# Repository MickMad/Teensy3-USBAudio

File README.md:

Teensy3-USBAudio
================

Transform a Teensy 3.0 in a USB compliant audio device

Software part
-------------------------

The `software` folder contains modified versions of some Teensy 3.0 USB core library.

First, in `/hardware/teensy` there's the board.txt file which has some added lines to properly show the "Audio" USB type in the Arduino IDE;

In `/hardware/teensy/teensy3` there are some USB core library files for the Teensy 3.0 with my Audio library patch.

The `usb_audio.c` and `usb_audio.h` files are the real Audio library, which is going to handle all the audio interface relevant stuff.

The `usb_desc.c` and `usb_desc.h` files contain USB descriptors-related stuff; some configuration stuff is in `usb_desc.h`, while the whole Audio interface descriptor is in `usb_audio.c`.

The `usb_dev.c` and `usb_dev.h` files contain low level USB control stuff; the only "major" modification until now is that there's no toggle between Data0 and Data1 PIDs when sending packets on the Audio Streaming interface, because Isochronous transfers only happen to use Data0 PIDs.

The `usb_inst.cpp` file contains all the USB application-specific library instances to be used in the sketches.

In `sketch` you'll find a sketch folder, which contains the sketch `BlinkAndTalk.ino`; this sketch instantiates an IntervalTimer, then waits until the host requests the Audio Interface to stream data; then it starts the timer to generate samples and streams them via USB.

I know the name BlinkAndTalk doesn't really fit the Audio functionality, but that started as a pure USB initialization debugging sketch that blinked and "talked" via SPI to an Arduino that was used as a Serial-to-USB converter, to let me know what was actually happening during the USB initialization and interrupt routines :D

Right now, the descriptor configures the Teensy as a device called Teensy Audio (but it may show as Teensyduino MIDI on Linux, don't know why), and it will show up as a Mono Microphone input, 8KHz , 16 bits per sample.
The sketch SHOULD be sending a 1 KHz square wave, although recording it in Audacity @ 8 KHz shows a 1KHz carrier with a 4 KHz triangle over it, even if a USB packet analyzer shows the same data you see in the sketch (0x8000 - 0x7fff).
I still got to understand why this happens; I've tried filling the packets LSB first, MSB first, don't-care-just-write-stuff first, I just can't get it to show as a square wave. Though, if you record in Audacity @ 44100 or whatever it's not 8KHz, it shows a nice square wave. Gotta investigate further.

All the stuff inside the software folder must be placed in the same directory found in your arudino folder.

***WARNING: MAKE A BACKUP COPY OF THOSE FILES IN YOUR ARDUINO FOLDER BEFORE MAKING ANY CHANGES.***

I know my mods are harmless, and that they are never ever used unless you explicitly set the Audio USB Type when compiling, but you should backup anyway, I don't want to be blamed for anything :V

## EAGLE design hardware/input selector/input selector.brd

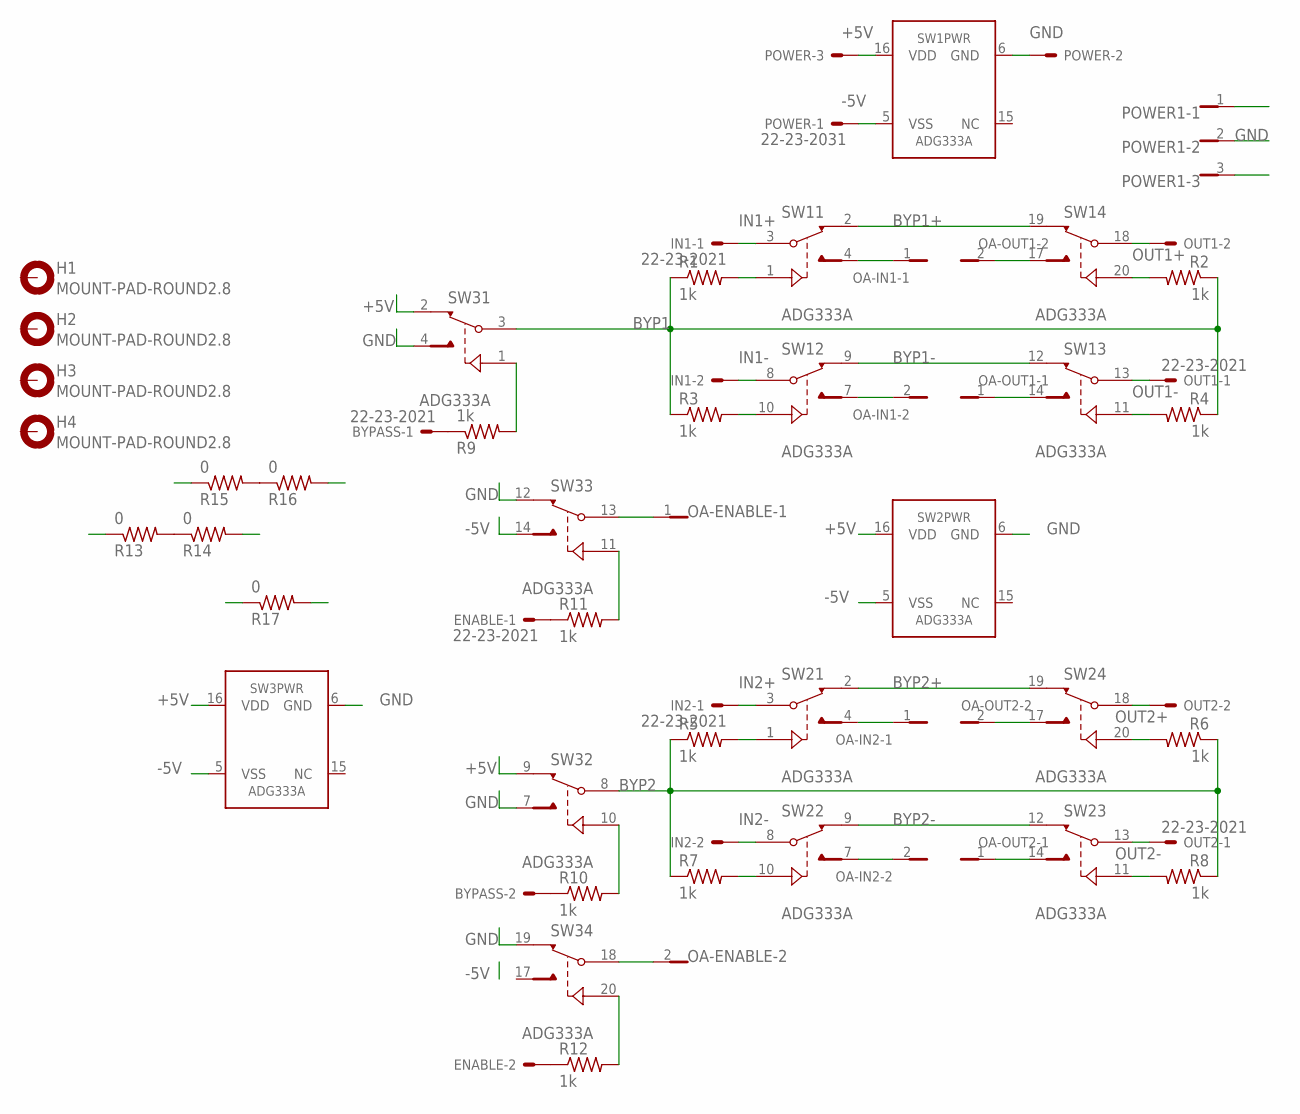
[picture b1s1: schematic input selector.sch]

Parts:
BYPASS: 22-23-2021
ENABLE: 22-23-2021
H1, H2, H3, H4: MOUNT-PAD-ROUND2.8; 2,8-PAD
IN1, IN2: 22-23-2021
OA-ENABLE: FE02-1
OA-IN1, OA-IN2: FE02-1
OA-OUT1, OA-OUT2: FE02-1
OUT1, OUT2: 22-23-2021
POWER: 22-23-2031
POWER1: FE03-1
R1, R2, R3, R4, R5, R6, R7, R8, R9, R10, R11, R12: 1k; R0603
R13, R14, R15, R16, R17: 0; R0603
SW1, SW2, SW3: ADG333A; SSOP20

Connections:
+5V: POWER.3, POWER1.1, R17.1, R17.2, SW1.16 (VDD), SW2.16 (VDD), SW3.2 (A), SW3.9 (A), SW3.16 (VDD)
-5V: POWER.1, POWER1.3, SW1.5 (VSS), SW2.5 (VSS), SW3.5 (VSS), SW3.14 (B)
BYP1: R1.1, R2.1, R3.1, R4.1, R13.1, R14.2, SW3.3 (D)
BYP1+: SW1.2 (A), SW1.19 (A)
BYP1-: SW1.9 (A), SW1.12 (A)
BYP2: R5.1, R6.1, R7.1, R8.1, R15.1, R16.2, SW3.8 (D)
BYP2+: SW2.2 (A), SW2.19 (A)
BYP2-: SW2.9 (A), SW2.12 (A)
GND: POWER.2, POWER1.2, SW1.6 (GND), SW2.6 (GND), SW3.4 (B), SW3.6 (GND), SW3.7 (B), SW3.12 (A), SW3.19 (A)
IN1+: IN1.1, SW1.3 (D)
IN1-: IN1.2, SW1.8 (D)
IN2+: IN2.1, SW2.3 (D)
IN2-: IN2.2, SW2.8 (D)
unnamed: ENABLE.2, R12.1
unnamed: R1.2, SW1.1 (IN)
unnamed: R5.2, SW2.1 (IN)
unnamed: R3.2, SW1.10 (IN)
unnamed: ENABLE.1, R11.1
unnamed: R7.2, SW2.10 (IN)
unnamed: OA-ENABLE.2, SW3.18 (D)
unnamed: OA-ENABLE.1, SW3.13 (D)
unnamed: R9.2, SW3.1 (IN)
unnamed: R10.2, SW3.10 (IN)
unnamed: R11.2, SW3.11 (IN)
unnamed: R12.2, SW3.20 (IN)
unnamed: OA-IN1.1, SW1.4 (B)
unnamed: R15.2, R16.1
unnamed: R13.2, R14.1
unnamed: R6.2, SW2.20 (IN)
unnamed: R2.2, SW1.20 (IN)
unnamed: R8.2, SW2.11 (IN)
unnamed: R4.2, SW1.11 (IN)
unnamed: BYPASS.1, R9.1
unnamed: BYPASS.2, R10.1
OA-IN1-: OA-IN1.2, SW1.7 (B)
OA-IN2+: OA-IN2.1, SW2.4 (B)
OA-IN2-: OA-IN2.2, SW2.7 (B)
OA-OUT1: OA-OUT1.1, SW1.14 (B)
OA-OUT1+: OA-OUT1.2, SW1.17 (B)
OA-OUT2+: OA-OUT2.2, SW2.17 (B)
OA-OUT2-: OA-OUT2.1, SW2.14 (B)
OUT1+: OUT1.2, SW1.18 (D)
OUT1-: OUT1.1, SW1.13 (D)
OUT2+: OUT2.2, SW2.18 (D)
OUT2-: OUT2.1, SW2.13 (D)

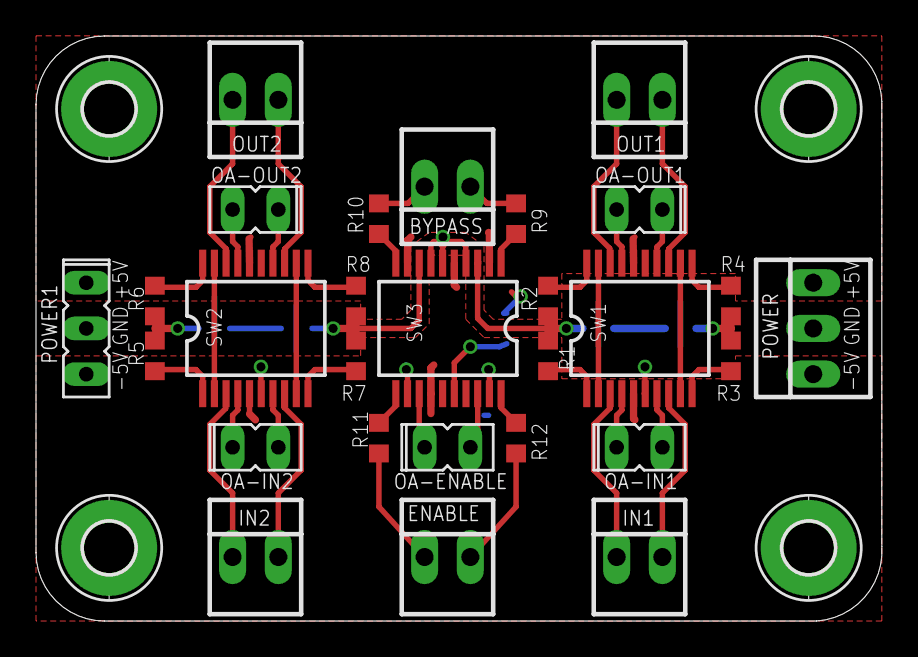
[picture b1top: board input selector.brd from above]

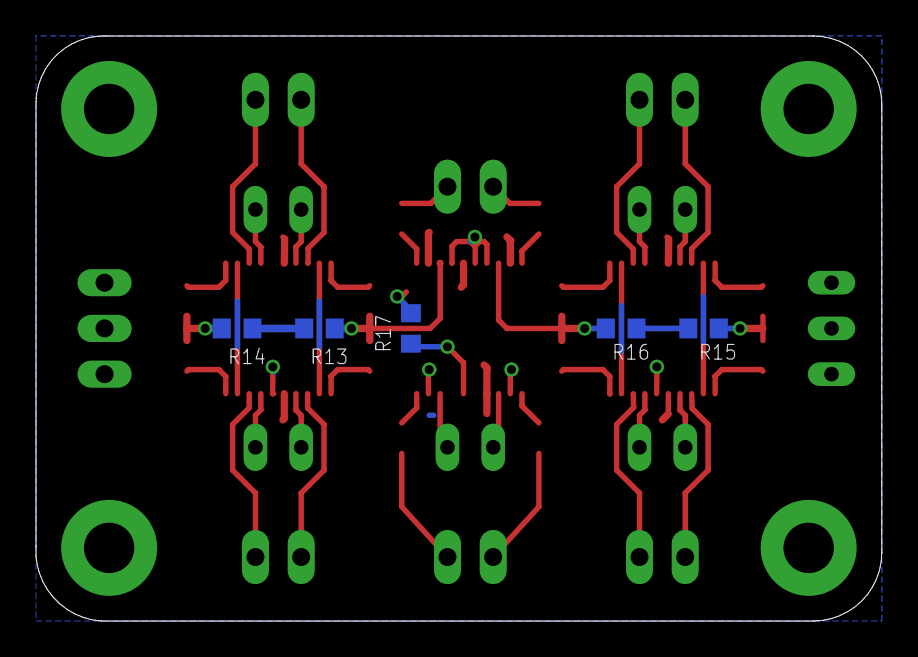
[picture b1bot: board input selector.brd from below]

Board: 2 copper layers, 47.0 x 32.5 mm, 37 parts (5 on the bottom side), 45 nets.

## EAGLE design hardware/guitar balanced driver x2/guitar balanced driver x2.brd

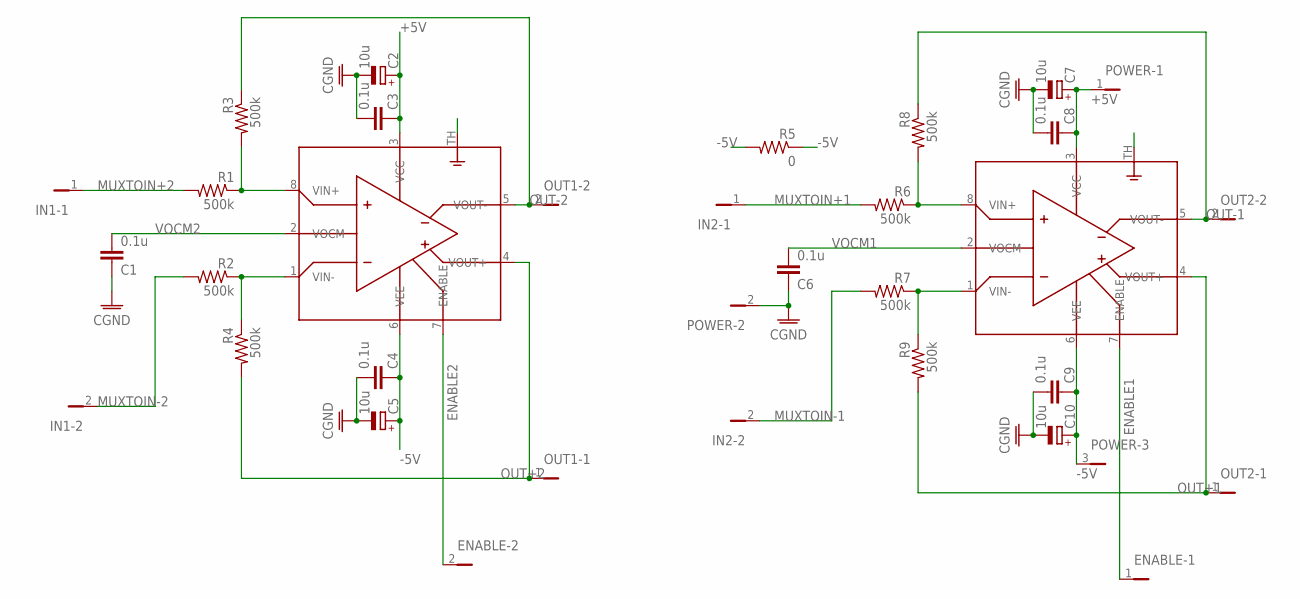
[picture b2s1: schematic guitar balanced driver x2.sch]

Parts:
C1, C3, C4, C6, C8, C9: 0.1u; C0603
C2, C5, C7, C10: 10u; PANASONIC_A
ENABLE: PINHD-1X2; 1X02
IN1, IN2: PINHD-1X2; 1X02
OA1, OA2: LME49724; S-PDSO-G08
OUT1, OUT2: PINHD-1X2; 1X02
POWER: PINHD-1X3; 1X03
R1, R2, R3, R4, R6, R7, R8, R9: 500k; R0603
R5: 0; R0603

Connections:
+5V: C2.+, C3.1, C7.+, C8.1, OA1.3 (VCC), OA2.3 (VCC), POWER.1
-5V: C4.1, C5.+, C9.1, C10.+, OA1.6 (VEE), OA1.TH (POWERPAD), OA2.6 (VEE), OA2.TH (POWERPAD), POWER.3, R5.1, R5.2
CGND: C1.1, C2.-, C3.2, C4.2, C5.-, C6.1, C7.-, C8.2, C9.2, C10.-, POWER.2
ENABLE1: ENABLE.1, OA2.7 (ENABLE)
ENABLE2: ENABLE.2, OA1.7 (ENABLE)
MUXTOIN+1: IN2.1, R6.2
MUXTOIN+2: IN1.1, R1.2
MUXTOIN-1: IN2.2, R7.2
MUXTOIN-2: IN1.2, R2.2
OUT+1: OA2.4 (VOUT+), OUT2.1, R9.2
OUT+2: OA1.4 (VOUT+), OUT1.1, R4.2
OUT-1: OA2.5 (VOUT-), OUT2.2, R8.1
OUT-2: OA1.5 (VOUT-), OUT1.2, R3.1
VIN+1: OA2.8 (VIN+), R6.1, R8.2
VIN+2: OA1.8 (VIN+), R1.1, R3.2
VIN-1: OA2.1 (VIN-), R7.1, R9.1
VIN-2: OA1.1 (VIN-), R2.1, R4.1
VOCM1: C6.2, OA2.2 (VOCM)
VOCM2: C1.2, OA1.2 (VOCM)

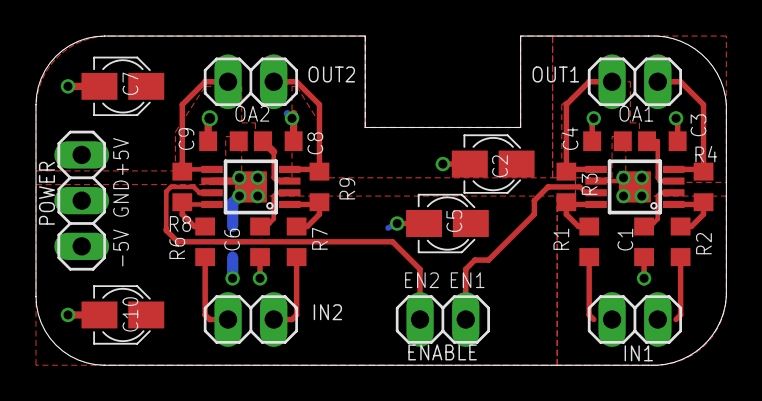
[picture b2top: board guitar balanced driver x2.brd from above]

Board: 2 copper layers, 38.4 x 18.3 mm, 27 parts (1 on the bottom side), 19 nets.

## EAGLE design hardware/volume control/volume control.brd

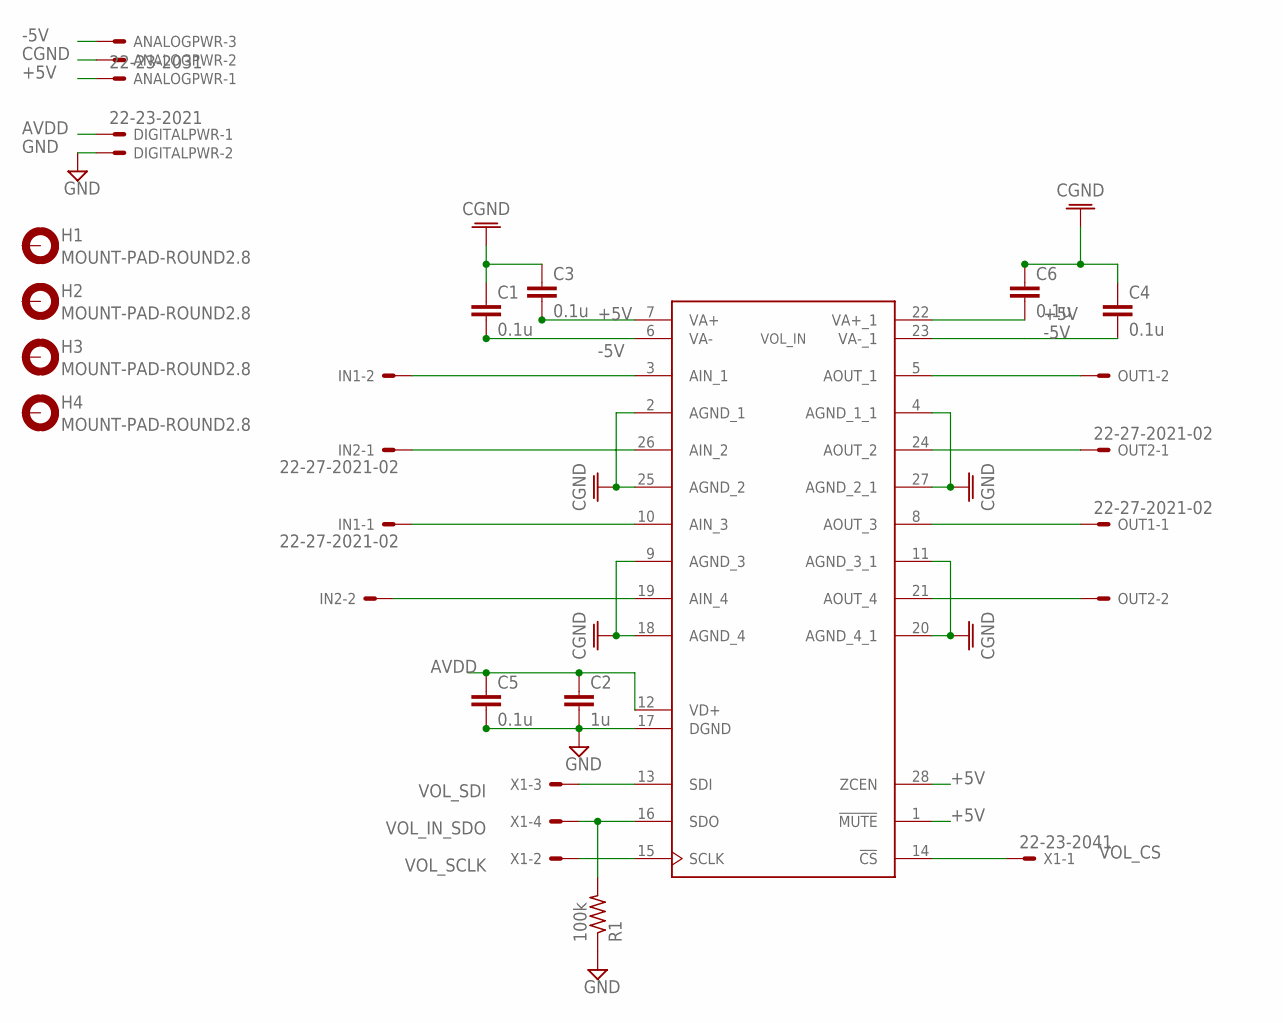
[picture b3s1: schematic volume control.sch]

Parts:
ANALOGPWR: 22-23-2031
C1, C3, C4, C5, C6: 0.1u; C0603
C2: 1u; C0603
DIGITALPWR: 22-23-2021
H1, H2, H3, H4: MOUNT-PAD-ROUND2.8; 2,8-PAD
IN1, IN2: 22-27-2021-02; 6410-02
OUT1, OUT2: 22-27-2021-02; 6410-02
R1: 100k; R0603
VOL_IN: PGA4311; DW_R-PDSO_G28
X1: 22-23-2041

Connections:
+5V: ANALOGPWR.1, C3.2, C6.2, VOL_IN.1 (!MUTE), VOL_IN.7 (VA+), VOL_IN.22 (VA+_1), VOL_IN.28 (ZCEN)
-5V: ANALOGPWR.3, C1.2, C4.2, VOL_IN.6 (VA-), VOL_IN.23 (VA-_1)
AVDD: C2.1, C5.1, DIGITALPWR.1, VOL_IN.12 (VD+)
CGND: ANALOGPWR.2, C1.1, C3.1, C4.1, C6.1, VOL_IN.2 (AGND_1), VOL_IN.4 (AGND_1_1), VOL_IN.9 (AGND_3), VOL_IN.11 (AGND_3_1), VOL_IN.18 (AGND_4), VOL_IN.20 (AGND_4_1), VOL_IN.25 (AGND_2), VOL_IN.27 (AGND_2_1)
GND: C2.2, C5.2, DIGITALPWR.2, R1.1, VOL_IN.17 (DGND)
unnamed: OUT1.1, VOL_IN.8 (AOUT_3)
unnamed: IN1.2, VOL_IN.3 (AIN_1)
unnamed: IN1.1, VOL_IN.10 (AIN_3)
unnamed: OUT2.1, VOL_IN.24 (AOUT_2)
unnamed: OUT1.2, VOL_IN.5 (AOUT_1)
unnamed: OUT2.2, VOL_IN.21 (AOUT_4)
unnamed: IN2.1, VOL_IN.26 (AIN_2)
unnamed: IN2.2, VOL_IN.19 (AIN_4)
VOL_CS: VOL_IN.14 (!CS), X1.1
VOL_IN_SDO: R1.2, VOL_IN.16 (SDO), X1.4
VOL_SCLK: VOL_IN.15 (SCLK), X1.2
VOL_SDI: VOL_IN.13 (SDI), X1.3

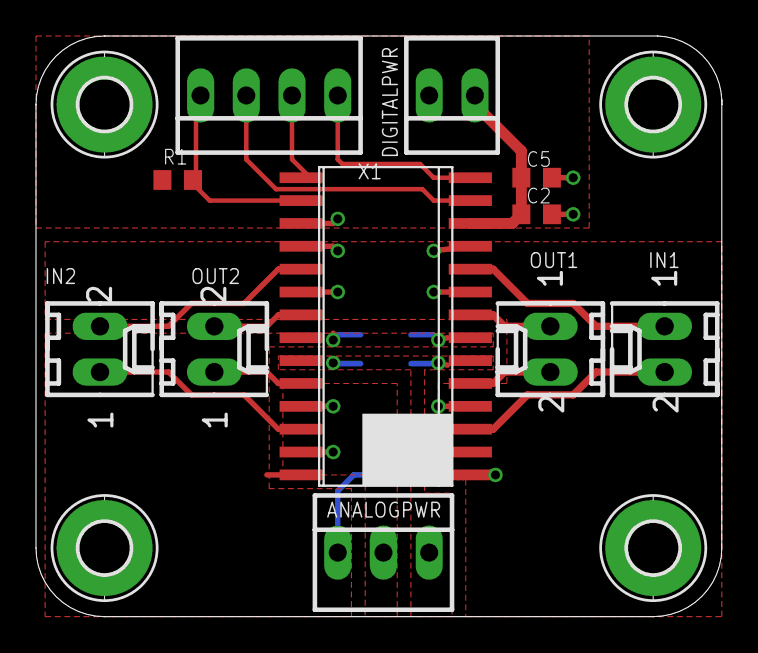
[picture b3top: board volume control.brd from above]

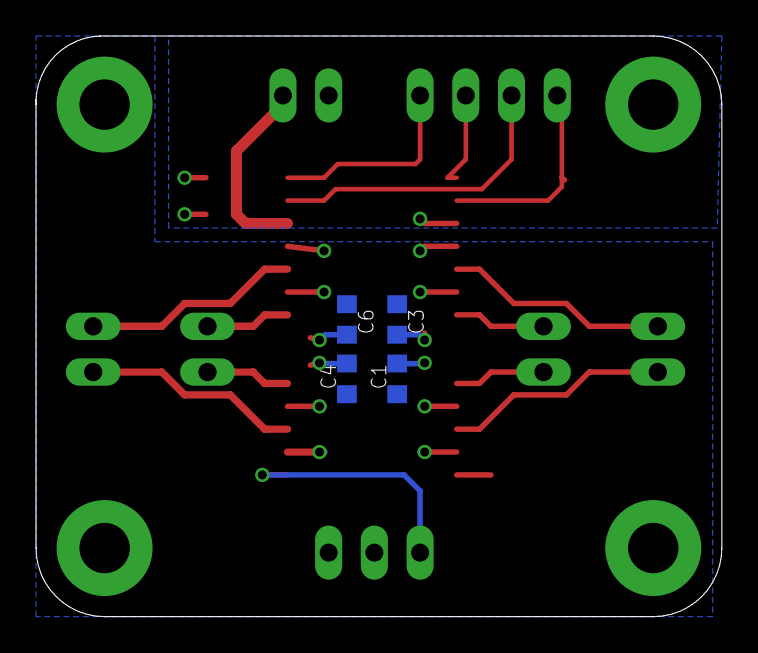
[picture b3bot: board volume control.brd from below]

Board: 2 copper layers, 38.1 x 32.3 mm, 19 parts (4 on the bottom side), 17 nets.

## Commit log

2013-09-18 first commit
    Added everything I've done until now
2013-09-18 Update README.md
    Formatted the readme.md file
2013-09-30 missing #incldue in WProgram.h
2013-10-03 major update
    -Fixed error at line 484 in usb_desc.c, the bSubFrameSize of the Type I
    Format Descriptor has been corrected to 2 bytes per sample
    -Deleted BlinkAndTalk.ino sketch: it has been replaced by two new
    example sketches, one to produce a squarewave, and one to produce a
    sinewave.
    -Configured the device to Synchronous mode operation: the sample
2013-10-03 fixed missing files in last commit
    Added new version of usb_audio.c and usb_audio.h; added function
    Audio.getSOF() and Audio.clearSOF() used in user sketch to check when to
    produce samples, and to clear the signal.
2013-10-03 missing line in usb_dev.h
    Fixed missing declaration of audio_SOF_signal in usb_dev.h
2013-10-07 added frequency control of the transmitted wave
    A pot on analog pin A0 now controls the note of the transmitted wave by
    indexing with its value a constant table filled with absolute
    frequencies of musical notes.
2013-10-07 usb_mem.h patch
    The USB memory management now supports for compile-time variable size
    USB packet buffers. MAX_PACKET_BUFFER_SIZE sets the maximum words
    available in a buffer, myType sets the words dimension.
2013-10-07 added compile-time definition of sampling rate
    The 3-byte coded sampling rate is used whenever the Teensy needs a
    3-byte coded sampling freq (like during sam_freq_ctrl_request or in
    config descriptor)
2013-10-07 usb_dev.h patch
    This patch uses the 3-byte coded sampling frequency for the
    sam_freq_ctrl_request; this patch also sets the size of the Buffer
    Descriptor Table entry for any endpoint to the value
    MAX_PACKET_BUFFER_SIZE that is to increase the maximum data payload per
    transaction.
2013-10-07 3-bytes coded sampling frequency in descriptor
    The descriptor now uses the defined 3-bytes coded sampling frequency
    during enumeration.
2013-10-07 #include "usb_desc.h" in usb_audio.c
    This include will serve to the audio library to access some useful
    constants, without having to redefine everything in every file.
2013-10-07 code formatting
2013-10-08 Updated sine sketch, Added more LUT's
    Added look-up tables available to use (2^ 8, 10, 12, 13). Added more
    comments. Changed code formatting to improve readability
2013-10-09 added support for 48 KHz stereo input
    The device now supports stereo 48 KHz; a patch to usb_mem.h and
    usb_dev..c has been made to enable support for USB buffers greater than
    64 bytes; patched usb_desc.h/c to contain info about the number of
    channels; patched sketch to do a pair of stereo samples for each
    iteratiion; to change bit resolution of the lookup table index, you only
    have to change LUT_INDEX_BITS in sine_lut_full.h; NOTE: sampling
2013-10-10 correct type definition for tx buffer pointer
    The buffer pointer used during transfers is now a pointer of type myType
    instead of fixed uint8_t
2013-10-23 descriptor changed for both in/out
    The Teensy 3.0 now enumerates as a full duplex stereo device.
2013-10-23 device stack supports requests for OUT interface
    - Added some callback functions for the OUT interface to let the device
    stack enable or disable the corresponding AudioStreaming interface
    - USB receive functions now support packets with size > 64 byte too.
2013-10-23 corrected MAX_PACKET_BUFFER_SIZE define
    This costant value was bigger than necessary.
2013-10-23 usb_malloc() modded
    This function now counts how many myType slots are left in memory,
    rather than how many uint8_t.
2013-10-23 Added functions to actually receive data
2013-10-23 New sketch for full duplex
    This sketch gets data from USB, sends it back to USB.
2015-11-18 Removed obsolete hardware designs, updated README
